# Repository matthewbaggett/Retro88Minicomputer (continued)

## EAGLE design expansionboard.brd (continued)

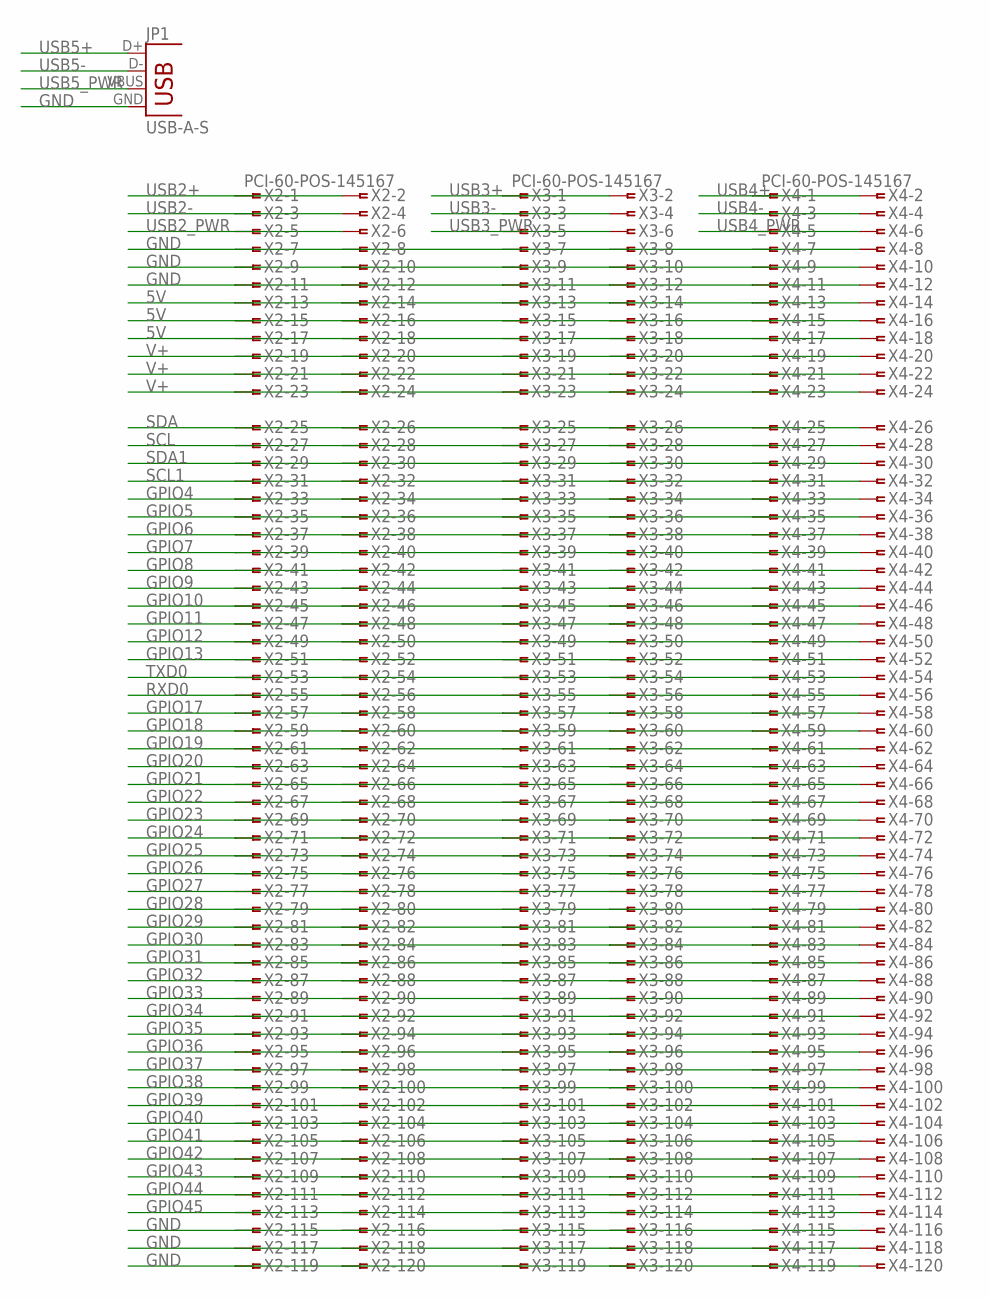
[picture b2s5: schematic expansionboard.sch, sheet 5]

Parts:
JP1: USB-A-S
X2, X3, X4: PCI-60-POS-145167; 145167-2

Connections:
5V: X2.13, X2.14, X2.15, X2.16, X2.17, X2.18, X3.13, X3.14, X3.15, X3.16, X3.17, X3.18, X4.13, X4.14, X4.15, X4.16, X4.17, X4.18; also elsewhere on the board
GND: JP1.GND, X2.7, X2.8, X2.9, X2.10, X2.11, X2.12, X2.115, X2.116, X2.117, X2.118, X2.119, X2.120, X3.7, X3.8, X3.9, X3.10, X3.11, X3.12, X3.115, X3.116, X3.117, X3.118, X3.119, X3.120, X4.7, X4.8, X4.9, X4.10, X4.11, X4.12, X4.115, X4.116, X4.117, X4.118, X4.119, X4.120; also elsewhere on the board
GPIO4: X2.33, X2.34, X3.33, X3.34, X4.33, X4.34; also elsewhere on the board
GPIO5: X2.35, X2.36, X3.35, X3.36, X4.35, X4.36; also elsewhere on the board
GPIO6: X2.37, X2.38, X3.37, X3.38, X4.37, X4.38; also elsewhere on the board
GPIO7: X2.39, X2.40, X3.39, X3.40, X4.39, X4.40; also elsewhere on the board
GPIO8: X2.41, X2.42, X3.41, X3.42, X4.41, X4.42; also elsewhere on the board
GPIO9: X2.43, X2.44, X3.43, X3.44, X4.43, X4.44; also elsewhere on the board
GPIO10: X2.45, X2.46, X3.45, X3.46, X4.45, X4.46; also elsewhere on the board
GPIO11: X2.47, X2.48, X3.47, X3.48, X4.47, X4.48; also elsewhere on the board
GPIO12: X2.49, X2.50, X3.49, X3.50, X4.49, X4.50; also elsewhere on the board
GPIO13: X2.51, X2.52, X3.51, X3.52, X4.51, X4.52; also elsewhere on the board
GPIO17: X2.57, X2.58, X3.57, X3.58, X4.57, X4.58; also elsewhere on the board
GPIO18: X2.59, X2.60, X3.59, X3.60, X4.59, X4.60; also elsewhere on the board
GPIO19: X2.61, X2.62, X3.61, X3.62, X4.61, X4.62; also elsewhere on the board
GPIO20: X2.63, X2.64, X3.63, X3.64, X4.63, X4.64; also elsewhere on the board
GPIO21: X2.65, X2.66, X3.65, X3.66, X4.65, X4.66; also elsewhere on the board
GPIO22: X2.67, X2.68, X3.67, X3.68, X4.67, X4.68; also elsewhere on the board
GPIO23: X2.69, X2.70, X3.69, X3.70, X4.69, X4.70; also elsewhere on the board
GPIO24: X2.71, X2.72, X3.71, X3.72, X4.71, X4.72; also elsewhere on the board
GPIO25: X2.73, X2.74, X3.73, X3.74, X4.73, X4.74; also elsewhere on the board
GPIO26: X2.75, X2.76, X3.75, X3.76, X4.75, X4.76; also elsewhere on the board
GPIO27: X2.77, X2.78, X3.77, X3.78, X4.77, X4.78; also elsewhere on the board
GPIO28: X2.79, X2.80, X3.79, X3.80, X4.79, X4.80; also elsewhere on the board
GPIO29: X2.81, X2.82, X3.81, X3.82, X4.81, X4.82; also elsewhere on the board
GPIO30: X2.83, X2.84, X3.83, X3.84, X4.83, X4.84; also elsewhere on the board
GPIO31: X2.85, X2.86, X3.85, X3.86, X4.85, X4.86; also elsewhere on the board
GPIO32: X2.87, X2.88, X3.87, X3.88, X4.87, X4.88; also elsewhere on the board
GPIO33: X2.89, X2.90, X3.89, X3.90, X4.89, X4.90; also elsewhere on the board
GPIO34: X2.91, X2.92, X3.91, X3.92, X4.91, X4.92; also elsewhere on the board
GPIO35: X2.93, X2.94, X3.93, X3.94, X4.93, X4.94; also elsewhere on the board
GPIO36: X2.95, X2.96, X3.95, X3.96, X4.95, X4.96; also elsewhere on the board
GPIO37: X2.97, X2.98, X3.97, X3.98, X4.97, X4.98; also elsewhere on the board
GPIO38: X2.99, X2.100, X3.99, X3.100, X4.99, X4.100; also elsewhere on the board
GPIO39: X2.101, X2.102, X3.101, X3.102, X4.101, X4.102; also elsewhere on the board
GPIO40: X2.103, X2.104, X3.103, X3.104, X4.103, X4.104; also elsewhere on the board
GPIO41: X2.105, X2.106, X3.105, X3.106, X4.105, X4.106; also elsewhere on the board
GPIO42: X2.107, X2.108, X3.107, X3.108, X4.107, X4.108; also elsewhere on the board
GPIO43: X2.109, X2.110, X3.109, X3.110, X4.109, X4.110; also elsewhere on the board
GPIO44: X2.111, X2.112, X3.111, X3.112, X4.111, X4.112; also elsewhere on the board
GPIO45: X2.113, X2.114, X3.113, X3.114, X4.113, X4.114; also elsewhere on the board
RXD0: X2.55, X2.56, X3.55, X3.56, X4.55, X4.56; also elsewhere on the board
SCL: X2.27, X2.28, X3.27, X3.28, X4.27, X4.28; also elsewhere on the board
SCL1: X2.31, X2.32, X3.31, X3.32, X4.31, X4.32; also elsewhere on the board
SDA: X2.25, X2.26, X3.25, X3.26, X4.25, X4.26; also elsewhere on the board
SDA1: X2.29, X2.30, X3.29, X3.30, X4.29, X4.30; also elsewhere on the board
TXD0: X2.53, X2.54, X3.53, X3.54, X4.53, X4.54; also elsewhere on the board
USB2+: X2.1, X2.2; also elsewhere on the board
USB2-: X2.3, X2.4; also elsewhere on the board
USB2_PWR: X2.5, X2.6; also elsewhere on the board
USB3+: X3.1, X3.2; also elsewhere on the board
USB3-: X3.3, X3.4; also elsewhere on the board
USB3_PWR: X3.5, X3.6; also elsewhere on the board
USB4+: X4.1, X4.2; also elsewhere on the board
USB4-: X4.3, X4.4; also elsewhere on the board
USB4_PWR: X4.5, X4.6; also elsewhere on the board
USB5+: JP1.D+; also elsewhere on the board
USB5-: JP1.D-; also elsewhere on the board
USB5_PWR: JP1.VBUS; also elsewhere on the board
V+: X2.19, X2.20, X2.21, X2.22, X2.23, X2.24, X3.19, X3.20, X3.21, X3.22, X3.23, X3.24, X4.19, X4.20, X4.21, X4.22, X4.23, X4.24; also elsewhere on the board

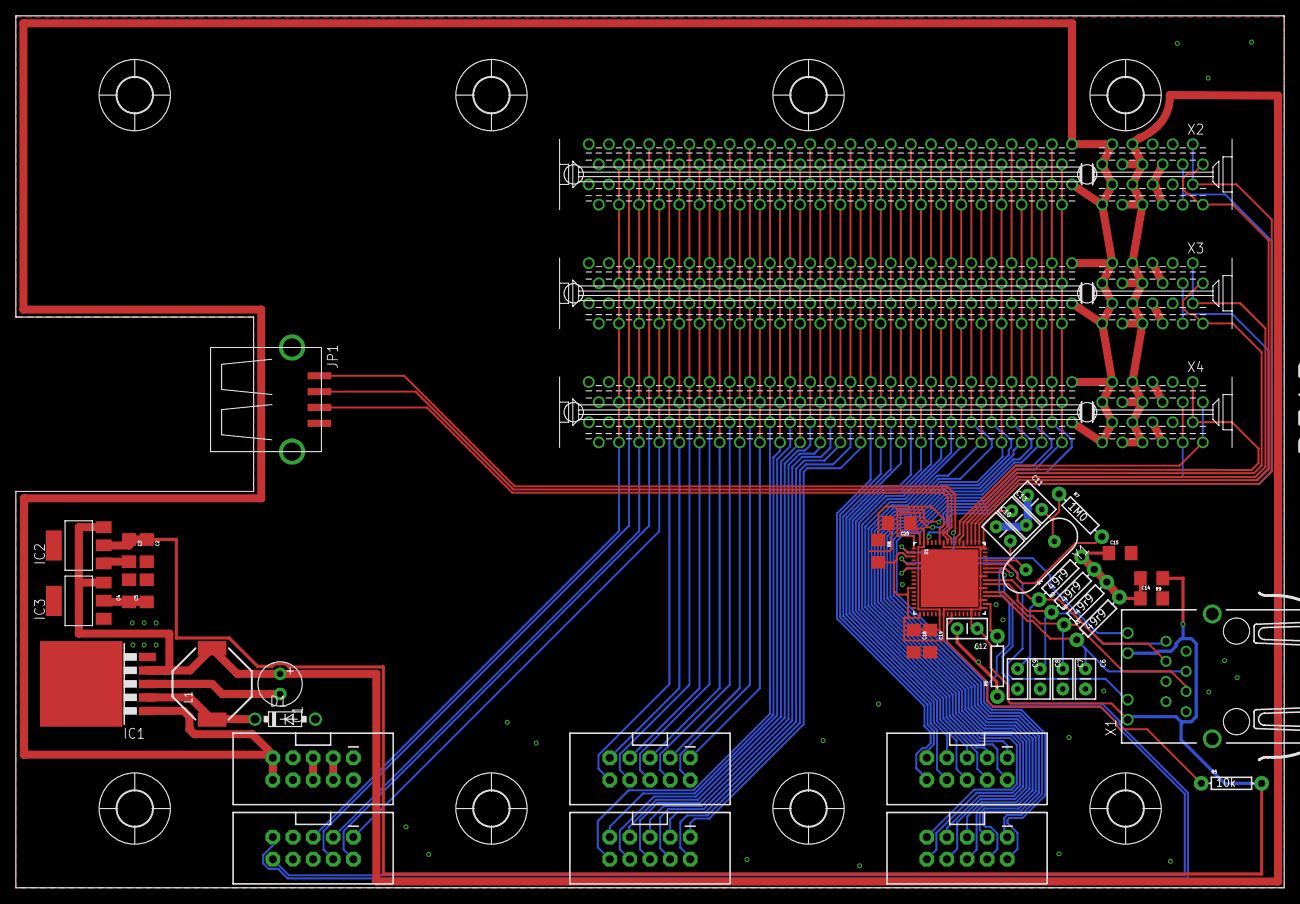
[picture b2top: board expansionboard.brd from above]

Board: 2 copper layers, 160.0 x 110.0 mm, 53 parts (0 on the bottom side), 81 nets.

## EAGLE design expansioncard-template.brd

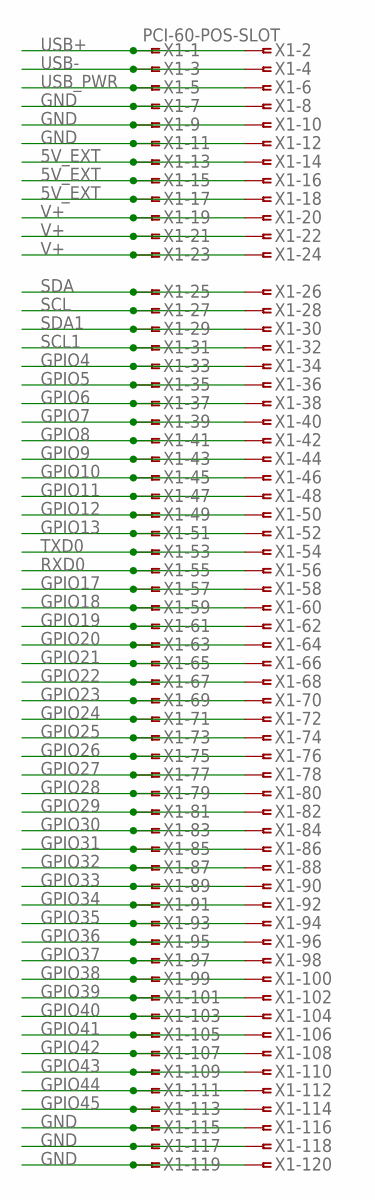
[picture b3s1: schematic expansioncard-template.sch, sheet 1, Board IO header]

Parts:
X1: PCI-60-POS-SLOT; PCI-SLOT-60

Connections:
5V_EXT: X1.13, X1.14, X1.15, X1.16, X1.17, X1.18; also elsewhere on the board
GND: X1.7, X1.8, X1.9, X1.10, X1.11, X1.12, X1.115, X1.116, X1.117, X1.118, X1.119, X1.120; also elsewhere on the board
GPIO4: X1.33, X1.34
GPIO5: X1.35, X1.36
GPIO6: X1.37, X1.38
GPIO7: X1.39, X1.40
GPIO8: X1.41, X1.42
GPIO9: X1.43, X1.44
GPIO10: X1.45, X1.46
GPIO11: X1.47, X1.48
GPIO12: X1.49, X1.50
GPIO13: X1.51, X1.52
GPIO17: X1.57, X1.58
GPIO18: X1.59, X1.60
GPIO19: X1.61, X1.62
GPIO20: X1.63, X1.64
GPIO21: X1.65, X1.66
GPIO22: X1.67, X1.68
GPIO23: X1.69, X1.70
GPIO24: X1.71, X1.72
GPIO25: X1.73, X1.74
GPIO26: X1.75, X1.76
GPIO27: X1.77, X1.78
GPIO28: X1.79, X1.80
GPIO29: X1.81, X1.82
GPIO30: X1.83, X1.84
GPIO31: X1.85, X1.86
GPIO32: X1.87, X1.88
GPIO33: X1.89, X1.90
GPIO34: X1.91, X1.92
GPIO35: X1.93, X1.94
GPIO36: X1.95, X1.96
GPIO37: X1.97, X1.98
GPIO38: X1.99, X1.100
GPIO39: X1.101, X1.102
GPIO40: X1.103, X1.104
GPIO41: X1.105, X1.106
GPIO42: X1.107, X1.108
GPIO43: X1.109, X1.110
GPIO44: X1.111, X1.112
GPIO45: X1.113, X1.114
RXD0: X1.55, X1.56
SCL: X1.27, X1.28
SCL1: X1.31, X1.32
SDA: X1.25, X1.26
SDA1: X1.29, X1.30
TXD0: X1.53, X1.54
USB+: X1.1, X1.2
USB-: X1.3, X1.4
USB_PWR: X1.5, X1.6
V+: X1.19, X1.20, X1.21, X1.22, X1.23, X1.24; also elsewhere on the board

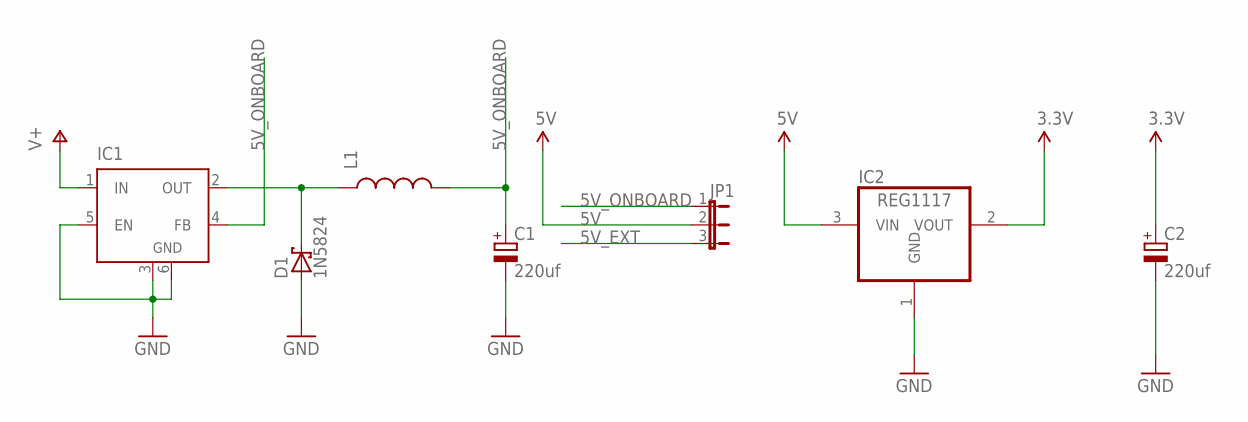
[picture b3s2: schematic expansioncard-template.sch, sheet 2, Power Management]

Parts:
C1, C2: 220uf; E2,5-6
D1: 1N5824; DO41-7.6
IC1: LM2596S; TO263-5
IC2: REG1117; SOT223
JP1: JP2E; JP2
L1: INDUCTORSRU1038; SRU1038

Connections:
3.3V: C2.+, IC2.2 (VOUT)
5V: IC2.3 (VIN), JP1.2
5V_EXT: JP1.3; also elsewhere on the board
5V_ONBOARD: C1.+, IC1.4 (FB), JP1.1, L1.2
GND: C1.-, C2.-, D1.A, IC1.3 (GND), IC1.5 (EN), IC1.6 (GND), IC2.1 (GND); also elsewhere on the board
V+: IC1.1 (IN); also elsewhere on the board
VOUT: D1.C, IC1.2 (OUT), L1.1

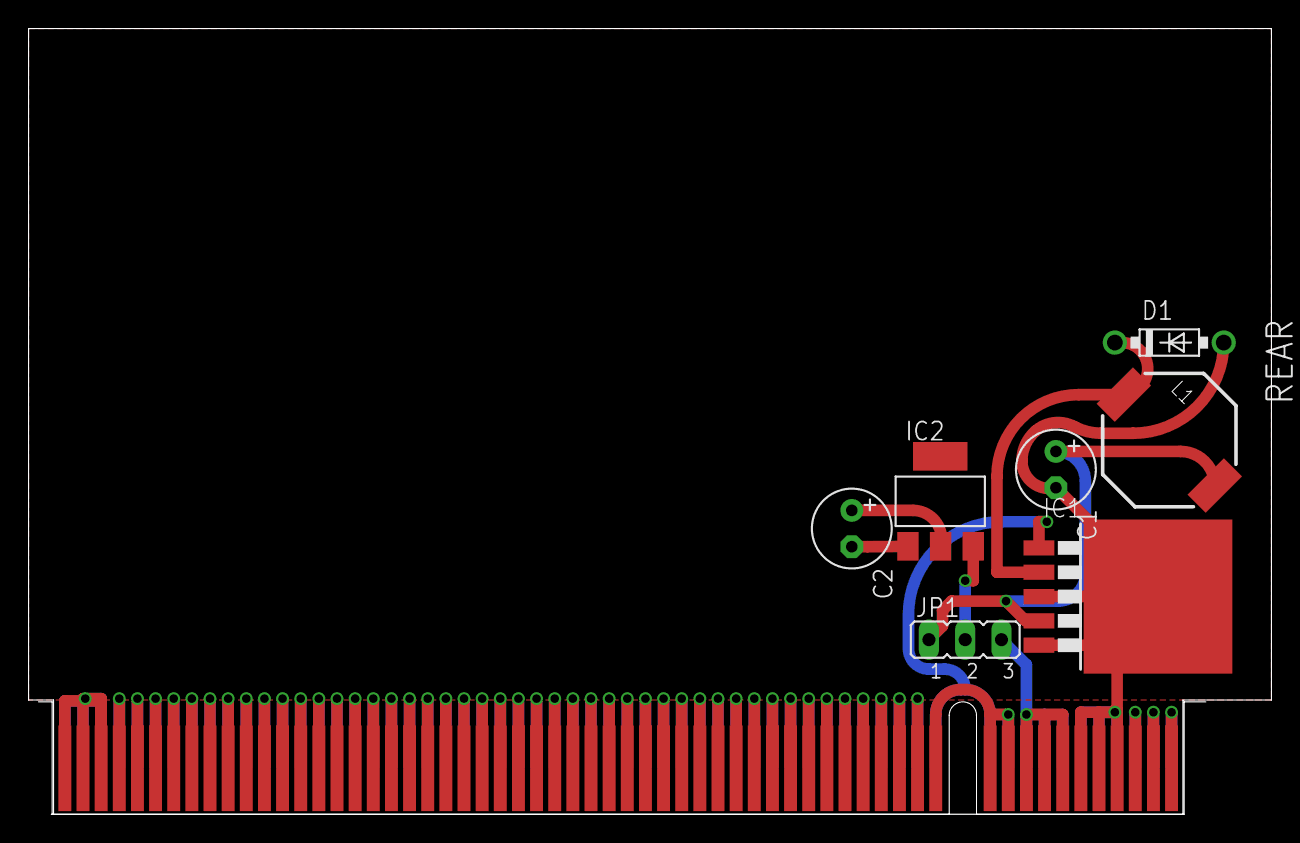
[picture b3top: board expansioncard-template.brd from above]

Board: 2 copper layers, 87.0 x 55.0 mm, 8 parts (1 on the bottom side), 55 nets.

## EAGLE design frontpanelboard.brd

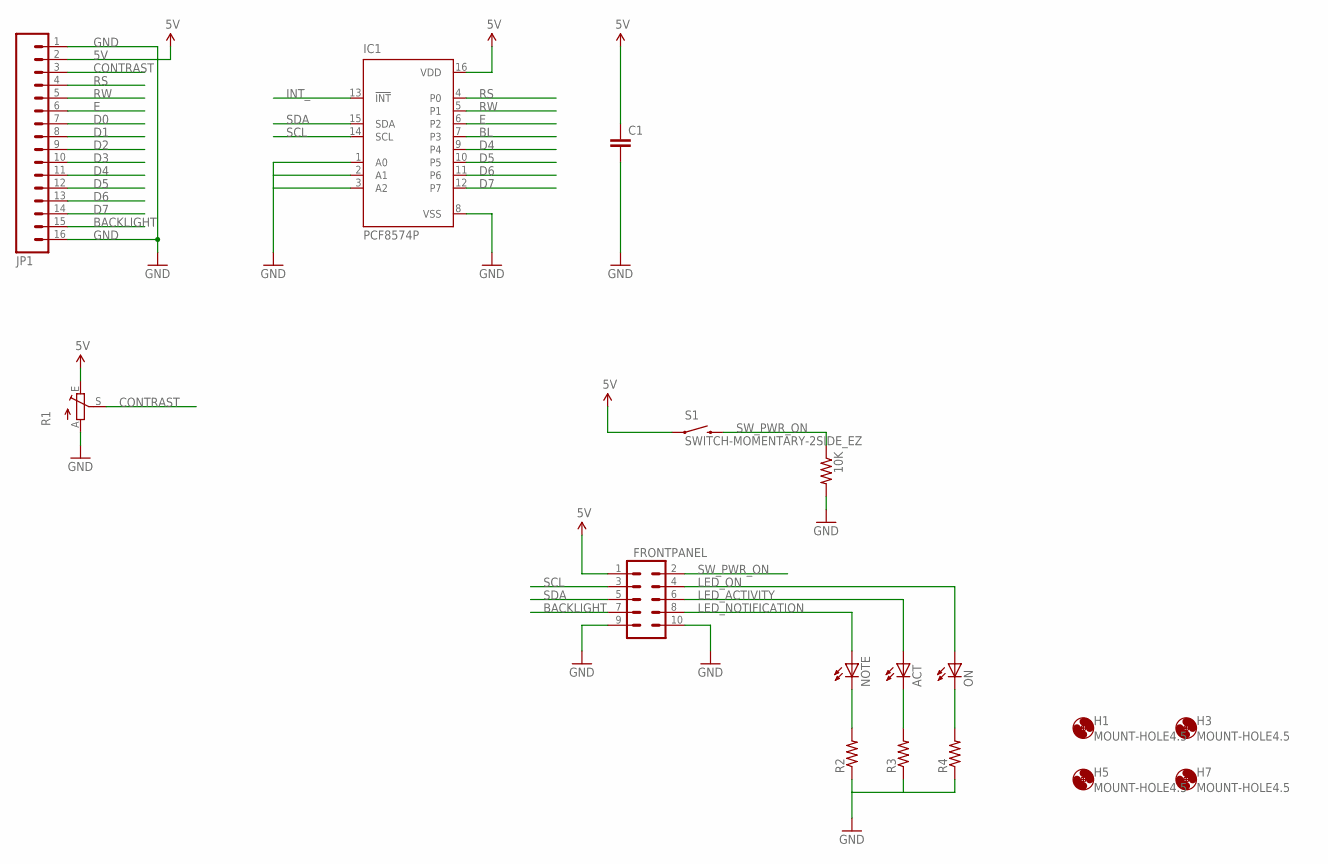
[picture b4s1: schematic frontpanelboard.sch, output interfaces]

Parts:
10K: RESISTOREZ; AXIAL-0.3EZ
ACT: LEDB155; Q62902-B155
C1: CAPEZ; CAP-PTH-SMALLEZ
FRONTPANEL: M05X2SHD_LOCK; 2X5-SHROUDED_LOCK
H1, H3, H5, H7: MOUNT-HOLE4.5; 4,5
IC1: PCF8574P; DIL16
JP1: M16LONGPADS; 1X16_LONGPADS
NOTE: LEDB155; Q62902-B155
ON: LEDB155; Q62902-B155
R1: TRIM_EU-LI10; LI10
R2, R3, R4: RESISTOREZ; AXIAL-0.3EZ
S1: SWITCH-MOMENTARY-2SIDE_EZ; TACTILE-PTH-SIDEEZ

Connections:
5V: C1.1, FRONTPANEL.1, IC1.16 (VDD), JP1.2, R1.E, S1.1
BACKLIGHT: FRONTPANEL.7, JP1.15
BL: IC1.7 (P3)
CONTRAST: JP1.3, R1.S
D0: JP1.7
D1: JP1.8
D2: JP1.9
D3: JP1.10
D4: IC1.9 (P4), JP1.11
D5: IC1.10 (P5), JP1.12
D6: IC1.11 (P6), JP1.13
D7: IC1.12 (P7), JP1.14
E: IC1.6 (P2), JP1.6
GND: 10K.P$2 (2), C1.2, FRONTPANEL.9, FRONTPANEL.10, IC1.1 (A0), IC1.2 (A1), IC1.3 (A2), IC1.8 (VSS), JP1.1, JP1.16, R1.A, R2.P$1 (1), R3.P$1 (1), R4.P$1 (1)
INT_: IC1.13 (!INT)
LED_ACTIVITY: ACT.A, FRONTPANEL.6
LED_NOTIFICATION: FRONTPANEL.8, NOTE.A
LED_ON: FRONTPANEL.4, ON.A
unnamed: ON.K (C), R4.P$2 (2)
unnamed: ACT.K (C), R3.P$2 (2)
unnamed: NOTE.K (C), R2.P$2 (2)
RS: IC1.4 (P0), JP1.4
RW: IC1.5 (P1), JP1.5
SCL: FRONTPANEL.3, IC1.14 (SCL)
SDA: FRONTPANEL.5, IC1.15 (SDA)
SW_PWR_ON: 10K.P$1 (1), FRONTPANEL.2, S1.2

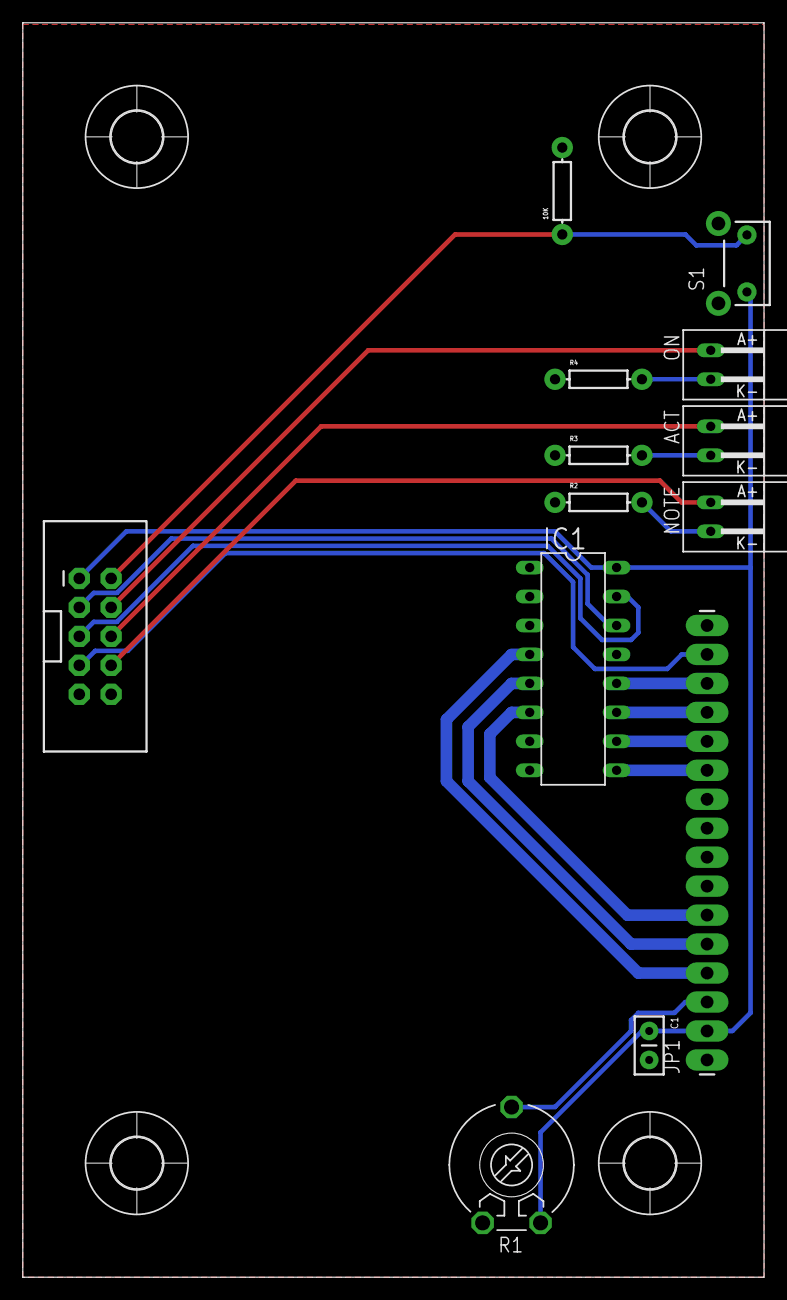
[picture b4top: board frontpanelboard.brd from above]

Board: 2 copper layers, 65.0 x 110.0 mm, 17 parts (0 on the bottom side), 20 nets.

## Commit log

2015-12-06 Initial schematic, missing USB, Ethernet, cheater HDMI jack
2015-12-06 Gitignore
2015-12-06 Initial board, probably scrap
2015-12-07 logicboard image
2015-12-14 Prototype expansion card with its own huge-ass power regulator.
2015-12-14 Updated gitignore
2015-12-14 for now, a complete logic board and expansion board until I find something wrong with it
2015-12-14 Adding borders to schematics
